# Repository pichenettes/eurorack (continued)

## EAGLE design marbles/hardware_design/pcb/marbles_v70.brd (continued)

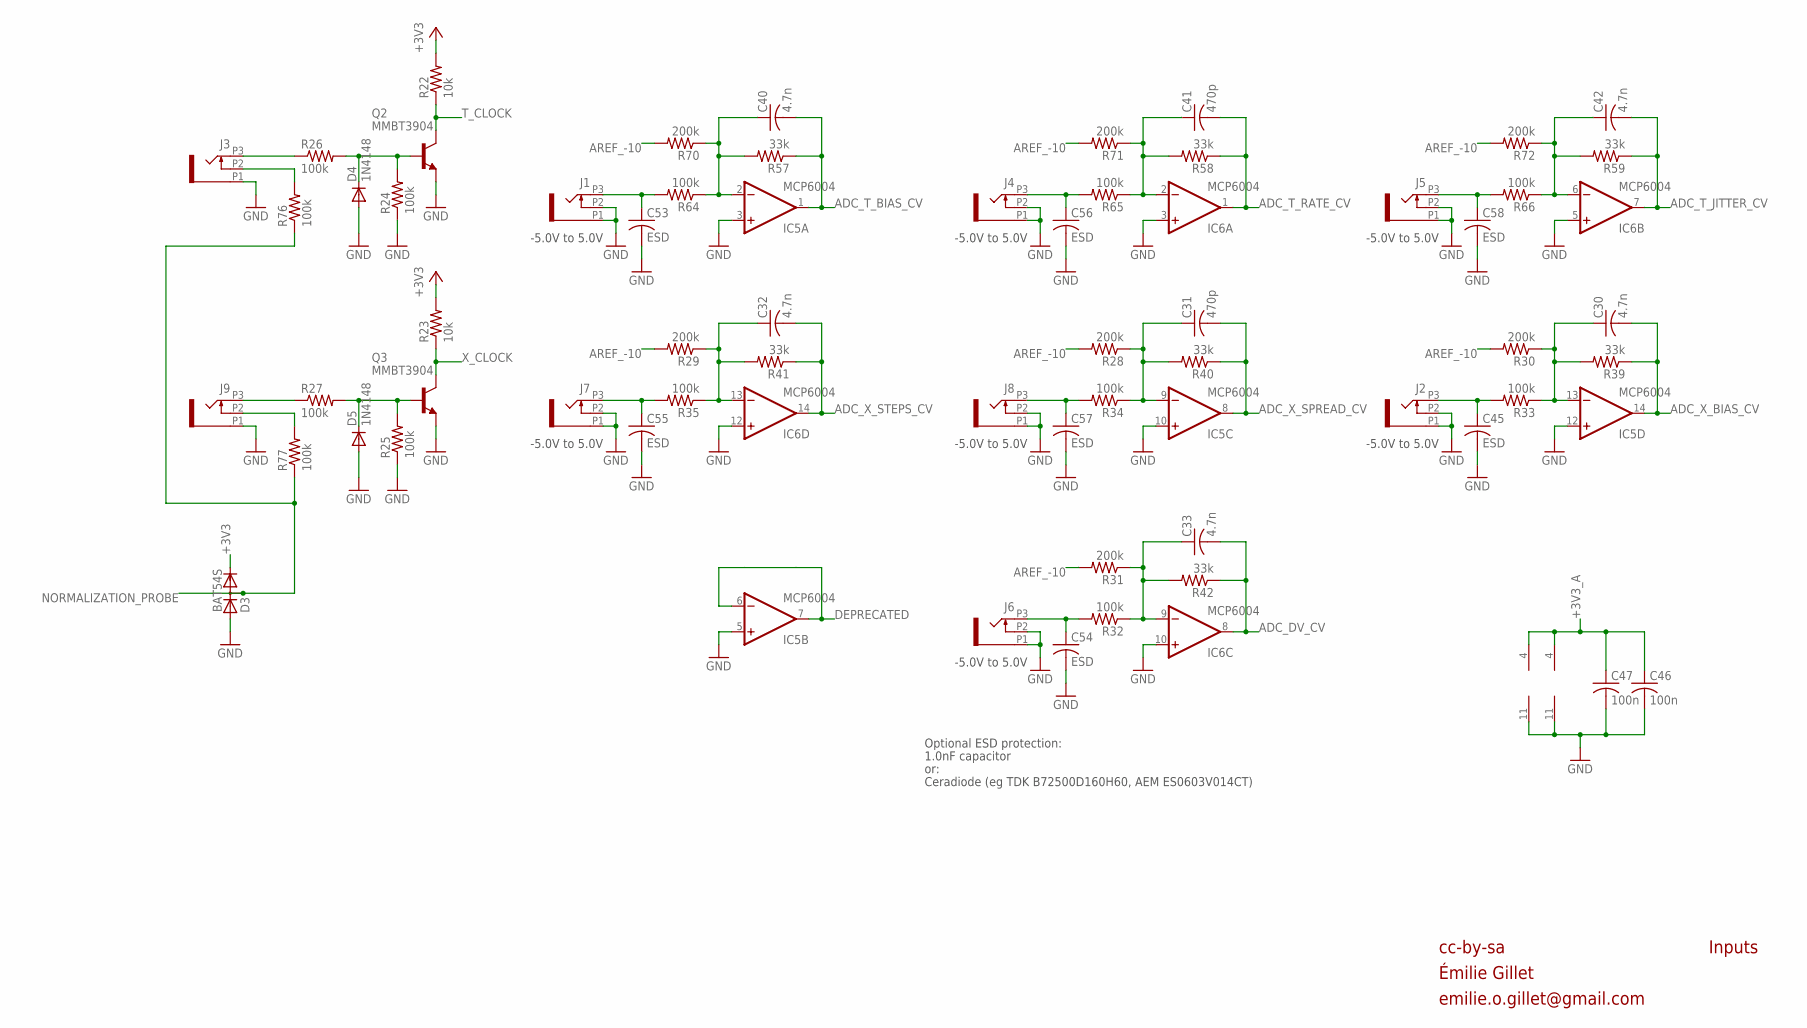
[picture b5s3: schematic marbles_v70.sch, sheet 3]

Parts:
C30, C32, C33, C40, C42: 4.7n; C0402
C31, C41: 470p; C0402
C45, C53, C54, C55, C56, C57, C58: ESD; C0603
C46, C47: 100n; C0402
D3: BAT54S; SOT23
D4, D5: 1N4148; SOD523
IC5, IC6: MCP6004; TSSOP14_065
J1, J2, J3, J4, J5, J6, J7, J8, J9: PJ301_THONKICONN6; WQP_PJ_301M6
Q2, Q3: MMBT3904; SOT23-BEC
R22, R23: 10k; R0402
R24, R25, R26, R27, R32, R33, R34, R35, R64, R65, R66, R76, R77: 100k; R0402
R28, R29, R30, R31, R70, R71, R72: 200k; R0402
R39, R40, R41, R42, R57, R58, R59: 33k; R0402

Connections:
+3V3: D3.2 (C), R22.2, R23.2; also elsewhere on the board
+3V3_A: C46.1, C47.1, IC5.4 (V+), IC6.4 (V+); also elsewhere on the board
ADC_DV_CV: C33.2, IC6.8 (OUT), R42.1; also elsewhere on the board
ADC_T_BIAS_CV: C40.2, IC5.1 (OUT), R57.1; also elsewhere on the board
ADC_T_JITTER_CV: C42.2, IC6.7 (OUT), R59.1; also elsewhere on the board
ADC_T_RATE_CV: C41.2, IC6.1 (OUT), R58.1; also elsewhere on the board
ADC_X_BIAS_CV: C30.2, IC5.14 (OUT), R39.1; also elsewhere on the board
ADC_X_SPREAD_CV: C31.2, IC5.8 (OUT), R40.1; also elsewhere on the board
ADC_X_STEPS_CV: C32.2, IC6.14 (OUT), R41.1; also elsewhere on the board
AREF_-10: R28.2, R29.2, R30.2, R31.2, R70.2, R71.2, R72.2; also elsewhere on the board
DEPRECATED: IC5.6 (-IN), IC5.7 (OUT)
GND: C45.2, C46.2, C47.2, C53.2, C54.2, C55.2, C56.2, C57.2, C58.2, D3.1 (A), D4.A, D5.A, IC5.3 (+IN), IC5.5 (+IN), IC5.10 (+IN), IC5.11 (V-), IC5.12 (+IN), IC6.3 (+IN), IC6.5 (+IN), IC6.10 (+IN), IC6.11 (V-), IC6.12 (+IN), J1.P1 (1), J1.P2 (2), J2.P1 (1), J2.P2 (2), J3.P1 (1), J4.P1 (1), J4.P2 (2), J5.P1 (1), J5.P2 (2), J6.P1 (1), J6.P2 (2), J7.P1 (1), J7.P2 (2), J8.P1 (1), J8.P2 (2), J9.P1 (1), Q2.E, Q3.E, R24.1, R25.1; also elsewhere on the board
MORPH_IN: C53.1, J1.P3 (3), R64.2
MORPH_IN1: C55.1, J7.P3 (3), R35.2
MORPH_IN3: C56.1, J4.P3 (3), R65.2
MORPH_IN4: C57.1, J8.P3 (3), R34.2
MORPH_IN5: C54.1, J6.P3 (3), R32.2
MORPH_IN6: C58.1, J5.P3 (3), R66.2
MORPH_IN7: C45.1, J2.P3 (3), R33.2
unnamed: C41.1, IC6.2 (-IN), R58.2, R65.1, R71.1
unnamed: C40.1, IC5.2 (-IN), R57.2, R64.1, R70.1
unnamed: C42.1, IC6.6 (-IN), R59.2, R66.1, R72.1
unnamed: C31.1, IC5.9 (-IN), R28.1, R34.1, R40.2
unnamed: C30.1, IC5.13 (-IN), R30.1, R33.1, R39.2
unnamed: C32.1, IC6.13 (-IN), R29.1, R35.1, R41.2
unnamed: C33.1, IC6.9 (-IN), R31.1, R32.1, R42.2
unnamed: J9.P3 (3), R27.1
unnamed: J9.P2 (2), R77.2
unnamed: J3.P2 (2), R76.2
unnamed: D4.C, Q2.B, R24.2, R26.2
unnamed: D5.C, Q3.B, R25.2, R27.2
unnamed: J3.P3 (3), R26.1
NORMALIZATION_PROBE: D3.3 (AC), R76.1, R77.1; also elsewhere on the board
T_CLOCK: Q2.C, R22.1; also elsewhere on the board
X_CLOCK: Q3.C, R23.1; also elsewhere on the board

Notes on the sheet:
cc-by-sa
Inputs
-5.0V to 5.0V
Optional ESD protection:
1.0nF capacitor
or:
Ceradiode (eg TDK B72500D160H60, AEM ES0603V014CT)
Émilie Gillet
emilie.o.gillet@gmail.com

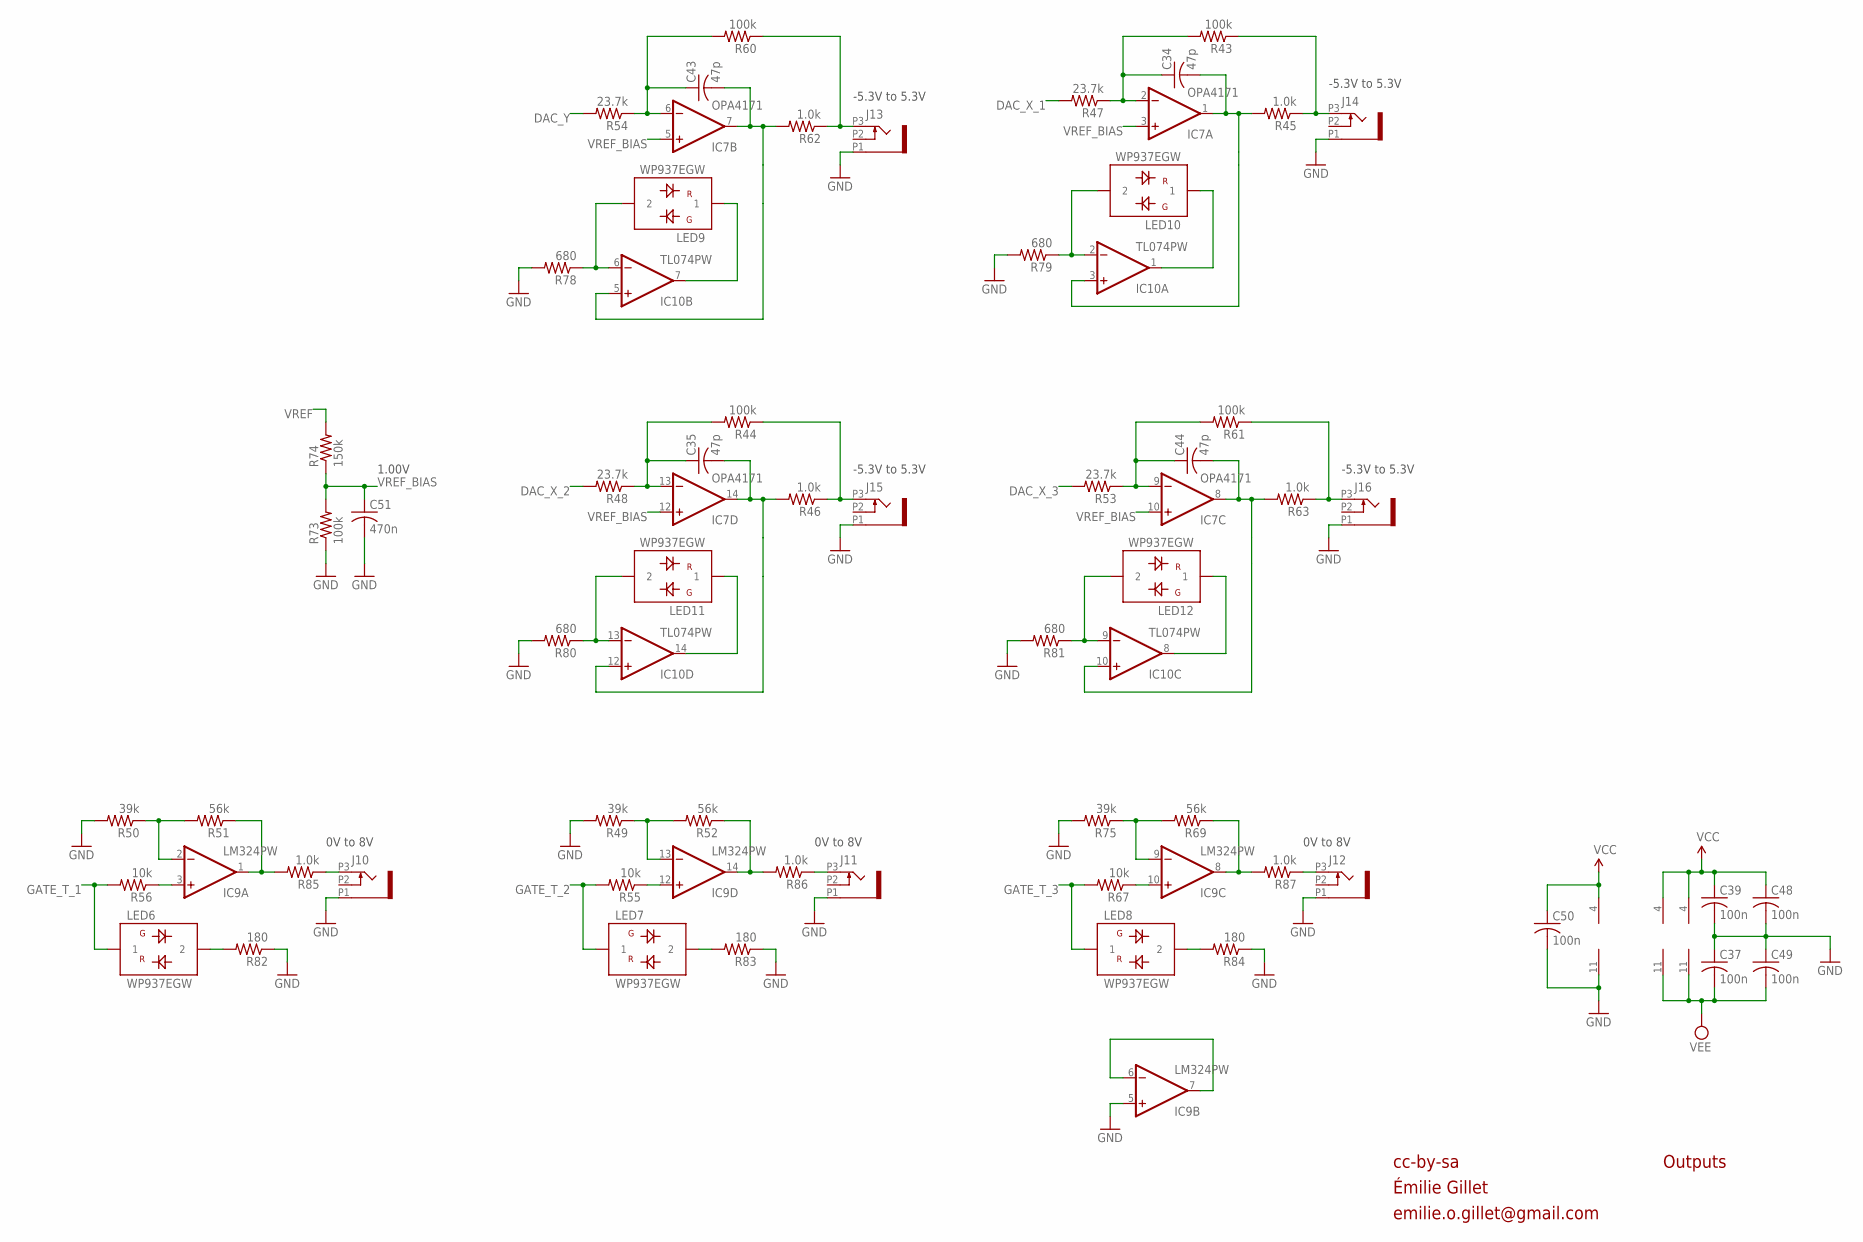
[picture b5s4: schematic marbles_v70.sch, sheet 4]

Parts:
C34, C35, C43, C44: 47p; C0402
C37, C39, C48, C49, C50: 100n; C0402
C51: 470n; C0402
IC7: OPA4171; TSSOP14_065
IC9: LM324PW; TSSOP14_065
IC10: TL074PW; TSSOP14_065
J10, J11, J12, J13, J14, J15, J16: PJ301_THONKICONN6; WQP_PJ_301M6
LED6, LED7, LED8, LED9, LED10, LED11, LED12: WP937EGW; LED3MM
R43, R44, R60, R61, R73: 100k; R0402
R45, R46, R62, R63, R85, R86, R87: 1.0k; R0603
R47, R48, R53, R54: 23.7k; R0402
R49, R50, R75: 39k; R0402
R51, R52, R69: 56k; R0402
R55, R56, R67: 10k; R0402
R74: 150k; R0402
R78, R79, R80, R81: 680; R0402
R82, R83, R84: 180; R0402

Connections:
DAC_X_1: R47.2; also elsewhere on the board
DAC_X_2: R48.2; also elsewhere on the board
DAC_X_3: R53.2; also elsewhere on the board
DAC_Y: R54.2; also elsewhere on the board
GATE_T_1: LED6.1, R56.2; also elsewhere on the board
GATE_T_2: LED7.1, R55.2; also elsewhere on the board
GATE_T_3: LED8.1, R67.2; also elsewhere on the board
GND: C37.1, C39.2, C48.2, C49.1, C50.2, C51.2, IC9.5 (+IN), IC9.11 (V-), J10.P1 (1), J11.P1 (1), J12.P1 (1), J13.P1 (1), J14.P1 (1), J15.P1 (1), J16.P1 (1), R49.2, R50.2, R73.1, R75.2, R78.2, R79.2, R80.2, R81.2, R82.1, R83.1, R84.1; also elsewhere on the board
unnamed: IC9.12 (+IN), R55.1
unnamed: IC9.1 (OUT), R51.1, R85.2
unnamed: J10.P3 (3), R85.1
unnamed: IC9.2 (-IN), R50.1, R51.2
unnamed: LED6.2, R82.2
unnamed: IC9.3 (+IN), R56.1
unnamed: IC9.6 (-IN), IC9.7 (OUT)
unnamed: IC9.14 (OUT), R52.1, R86.2
unnamed: IC9.13 (-IN), R49.1, R52.2
unnamed: IC9.10 (+IN), R67.1
unnamed: IC9.8 (OUT), R69.1, R87.2
unnamed: J11.P3 (3), R86.1
unnamed: J12.P3 (3), R87.1
unnamed: IC9.9 (-IN), R69.2, R75.1
unnamed: LED7.2, R83.2
unnamed: C43.2, IC7.7 (OUT), IC10.5 (+IN), R62.2
unnamed: LED8.2, R84.2
unnamed: J15.P3 (3), R44.1, R46.1
unnamed: J13.P3 (3), R60.1, R62.1
unnamed: C35.1, IC7.13 (-IN), R44.2, R48.1
unnamed: J16.P3 (3), R61.1, R63.1
unnamed: C44.1, IC7.9 (-IN), R53.1, R61.2
unnamed: C34.1, IC7.2 (-IN), R43.2, R47.1
unnamed: C43.1, IC7.6 (-IN), R54.1, R60.2
unnamed: J14.P3 (3), R43.1, R45.1
unnamed: IC10.6 (-IN), LED9.2, R78.1
unnamed: IC10.7 (OUT), LED9.1
unnamed: C34.2, IC7.1 (OUT), IC10.3 (+IN), R45.2
unnamed: IC10.2 (-IN), LED10.2, R79.1
unnamed: IC10.1 (OUT), LED10.1
unnamed: C35.2, IC7.14 (OUT), IC10.12 (+IN), R46.2
unnamed: IC10.13 (-IN), LED11.2, R80.1
unnamed: IC10.14 (OUT), LED11.1
unnamed: C44.2, IC7.8 (OUT), IC10.10 (+IN), R63.2
unnamed: IC10.9 (-IN), LED12.2, R81.1
unnamed: IC10.8 (OUT), LED12.1
VCC: C39.1, C48.1, C50.1, IC7.4 (V+), IC9.4 (V+), IC10.4 (V+); also elsewhere on the board
VEE: C37.2, C49.2, IC7.11 (V-), IC10.11 (V-); also elsewhere on the board
VREF: R74.2; also elsewhere on the board
VREF_BIAS: C51.1, IC7.3 (+IN), IC7.5 (+IN), IC7.10 (+IN), IC7.12 (+IN), R73.2, R74.1

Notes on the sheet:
-5.3V to 5.3V
0V to 8V
cc-by-sa
Outputs
1.00V
Émilie Gillet
emilie.o.gillet@gmail.com

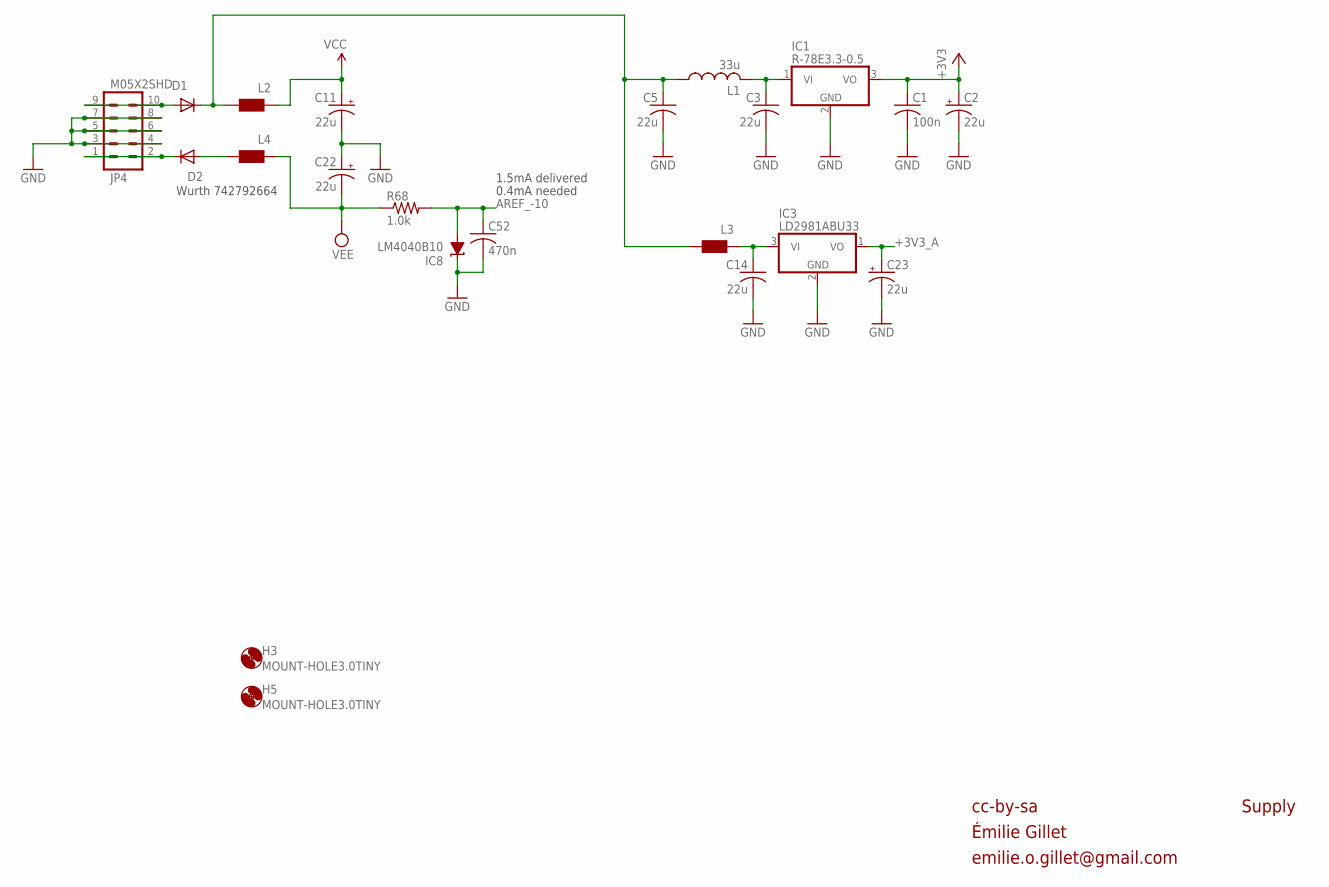
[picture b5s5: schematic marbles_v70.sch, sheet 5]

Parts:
C1: 100n; C0402
C2, C11, C22, C23: 22u; PANASONIC_C
C3, C5, C14: 22u; C1206
C52: 470n; C0402
D1, D2: 1N5819HW; SOD123
H3, H5: MOUNT-HOLE3.0TINY; 3,0TINY
IC1: R-78E3.3-0.5; WE78
IC3: LD2981ABU33; SOT89
IC8: LM4040B10; DBZ_R-PDSO-G3
JP4: M05X2SHD; 2X5-SHROUDED
L1: 33u; L2012C
L2, L3, L4: WE-CBF_0603; 0603
R68: 1.0k; R0402

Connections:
+3V3: C1.1, C2.+, IC1.3 (VO); also elsewhere on the board
+3V3_A: C23.+, IC3.1 (VO); also elsewhere on the board
AREF_-10: C52.1, IC8.2 (A), R68.2; also elsewhere on the board
GND: C1.2, C2.-, C3.2, C5.2, C11.-, C14.2, C22.+, C23.-, C52.2, IC1.2 (GND), IC3.2 (GND), IC8.1 (C), JP4.3, JP4.4, JP4.5, JP4.6, JP4.7, JP4.8; also elsewhere on the board
unnamed: C14.1, IC3.3 (VI), L3.1
unnamed: C5.1, D1.C, L1.1, L2.2, L3.2
unnamed: D2.A, L4.2
unnamed: C3.1, IC1.1 (VI), L1.2
unnamed: D1.A, JP4.9, JP4.10
unnamed: D2.C, JP4.1, JP4.2
VCC: C11.+, L2.1; also elsewhere on the board
VEE: C22.-, L4.1, R68.1; also elsewhere on the board

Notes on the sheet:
0.4mA needed
cc-by-sa
Supply
Wurth 742792664
1.5mA delivered
Émilie Gillet
emilie.o.gillet@gmail.com

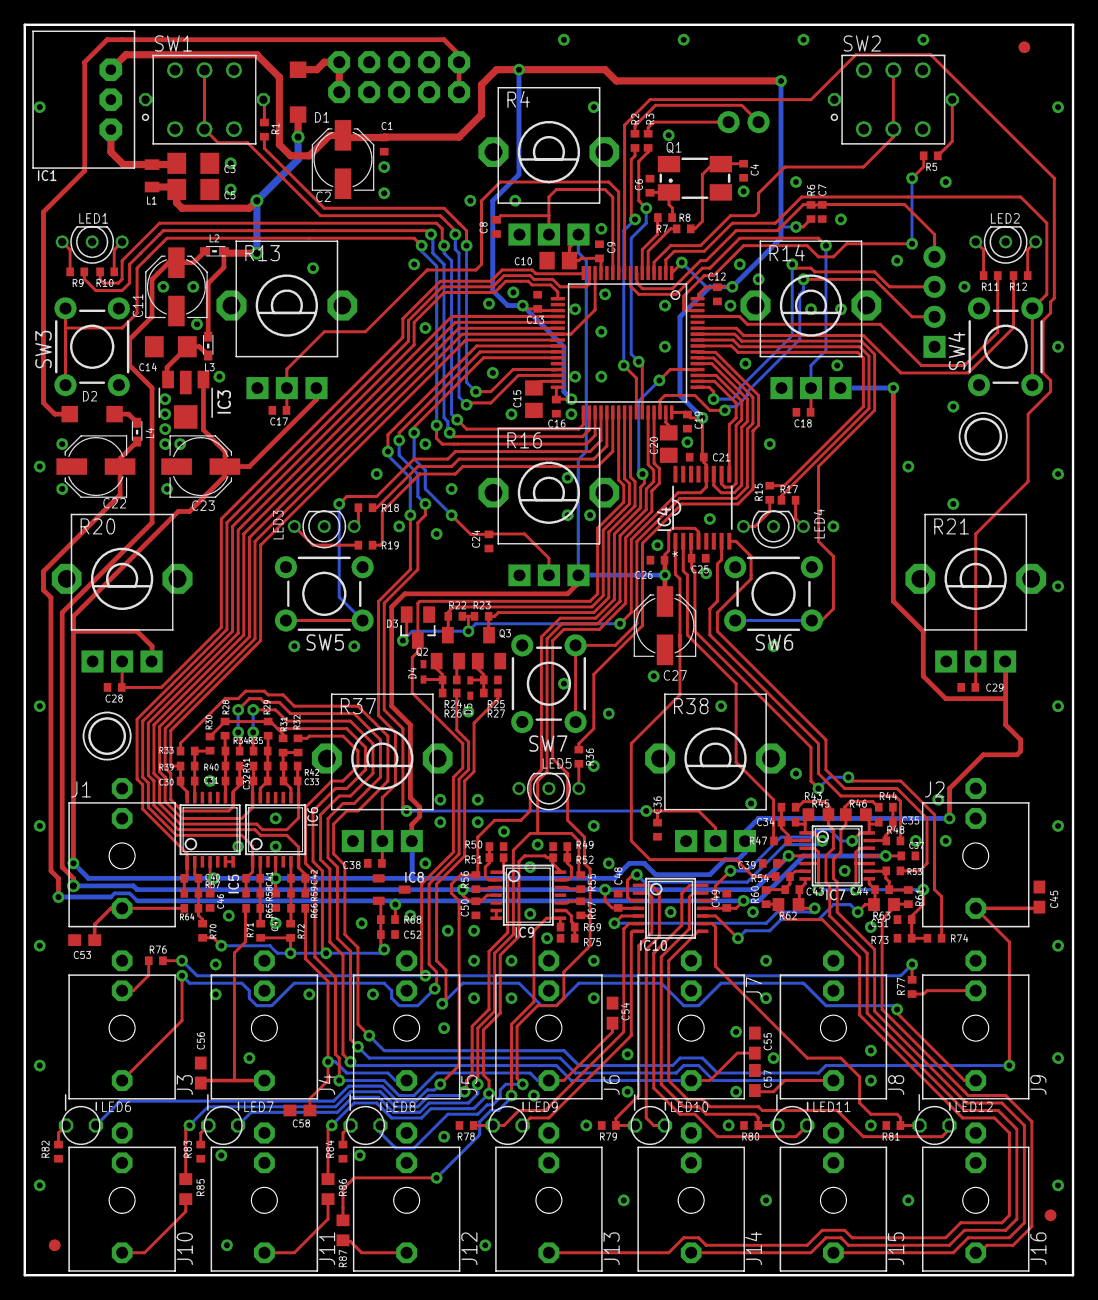
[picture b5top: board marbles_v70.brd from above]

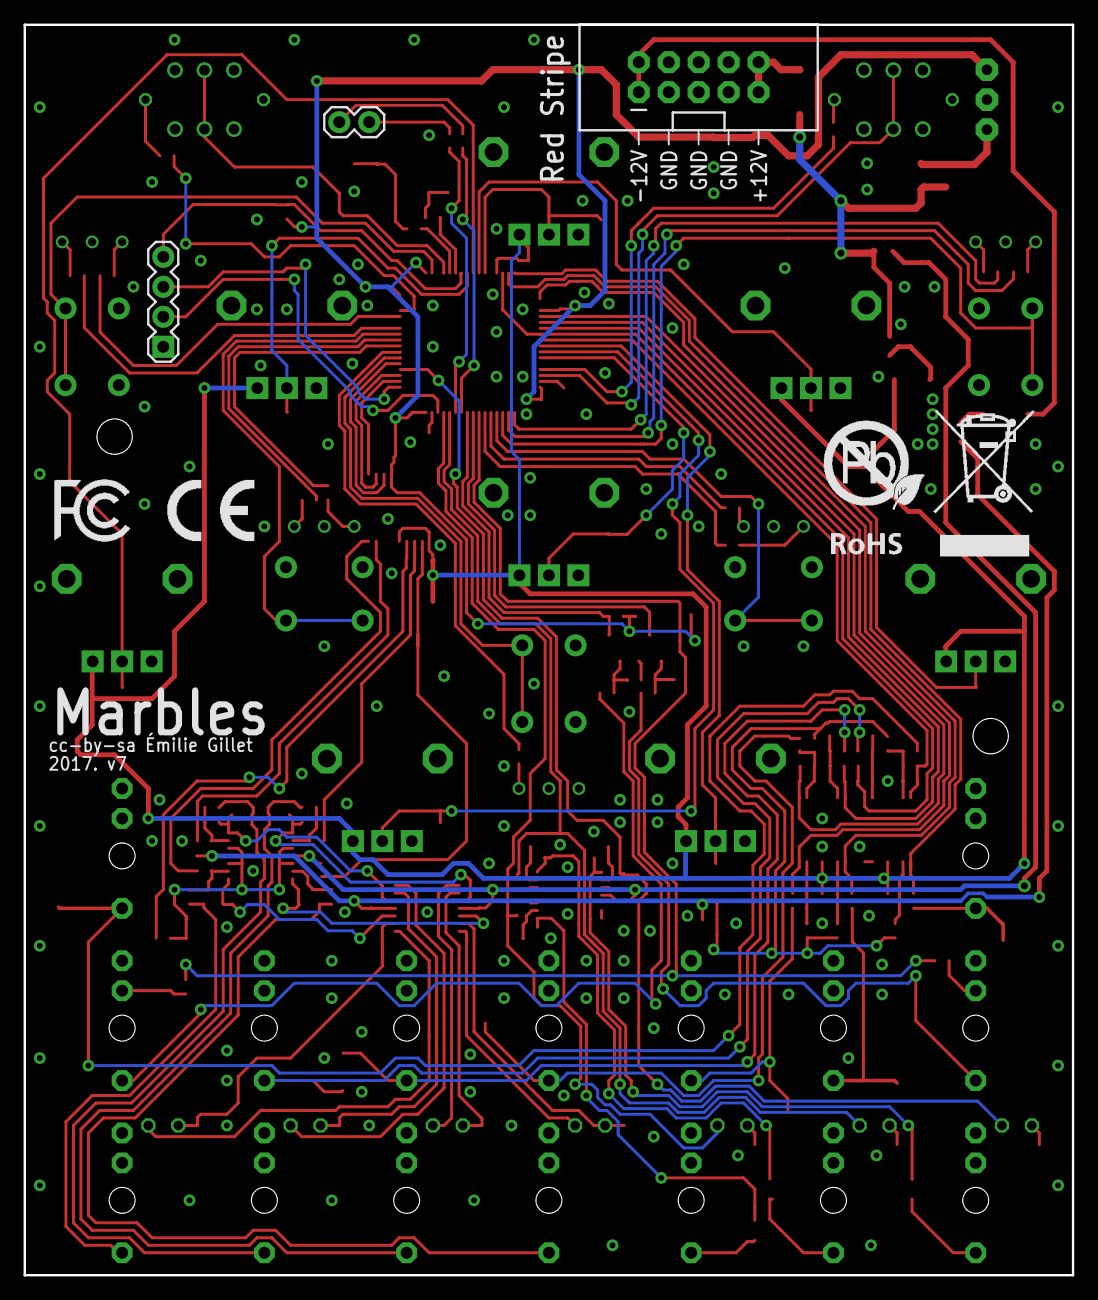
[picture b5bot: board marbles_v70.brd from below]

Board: 2 copper layers, 88.9 x 106.0 mm, 213 parts (6 on the bottom side), 141 nets.

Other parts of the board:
U$2: ROHS_BIG
U$4: CE_MEDIUM
U$5: FCC_MEDIUM
